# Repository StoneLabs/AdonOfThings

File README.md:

# AdonOfThings

Simple Project to turn an old industrial adon light into a multi purpose indicator light.

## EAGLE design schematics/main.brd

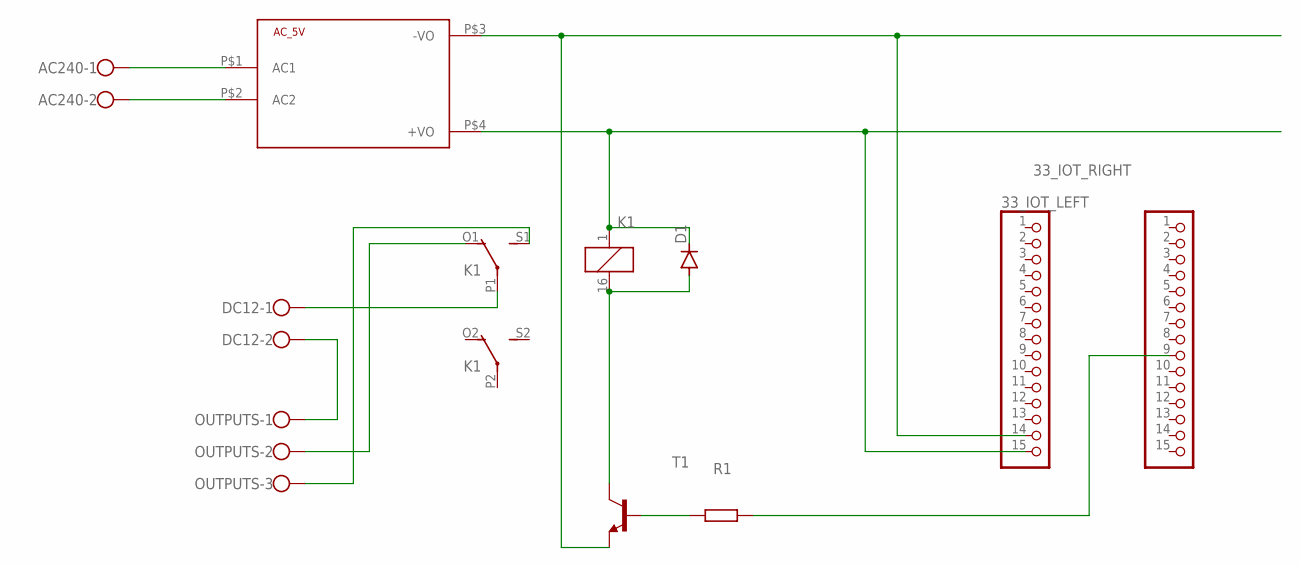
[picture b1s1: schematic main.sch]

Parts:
33_IOT_LEFT, 33_IOT_RIGHT: PINHD-1X15; 1X15
AC240: W237-102
AC_5V: HLK-PM013W; HLK-PM01
D1: 1N5060GP; DO15-12
DC12: W237-102
K1: 351
OUTPUTS: W237-103
R1: R-EU_0207/10; 0207/10
T1: 2N2222; TO18

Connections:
unnamed: AC240.1, AC_5V.P$1 (AC1)
unnamed: AC240.2, AC_5V.P$2 (AC2)
unnamed: R1.1, T1.2 (B)
unnamed: 33_IOT_LEFT.15, AC_5V.P$4 (+VO), D1.C, K1.1
unnamed: D1.A, K1.16 (2), T1.3 (C)
unnamed: DC12.2, OUTPUTS.1
unnamed: 33_IOT_LEFT.14, AC_5V.P$3 (-VO), T1.1 (E)
unnamed: DC12.1, K1.P1
unnamed: K1.O1 (O), OUTPUTS.2
unnamed: K1.S1 (S), OUTPUTS.3
unnamed: 33_IOT_RIGHT.9, R1.2

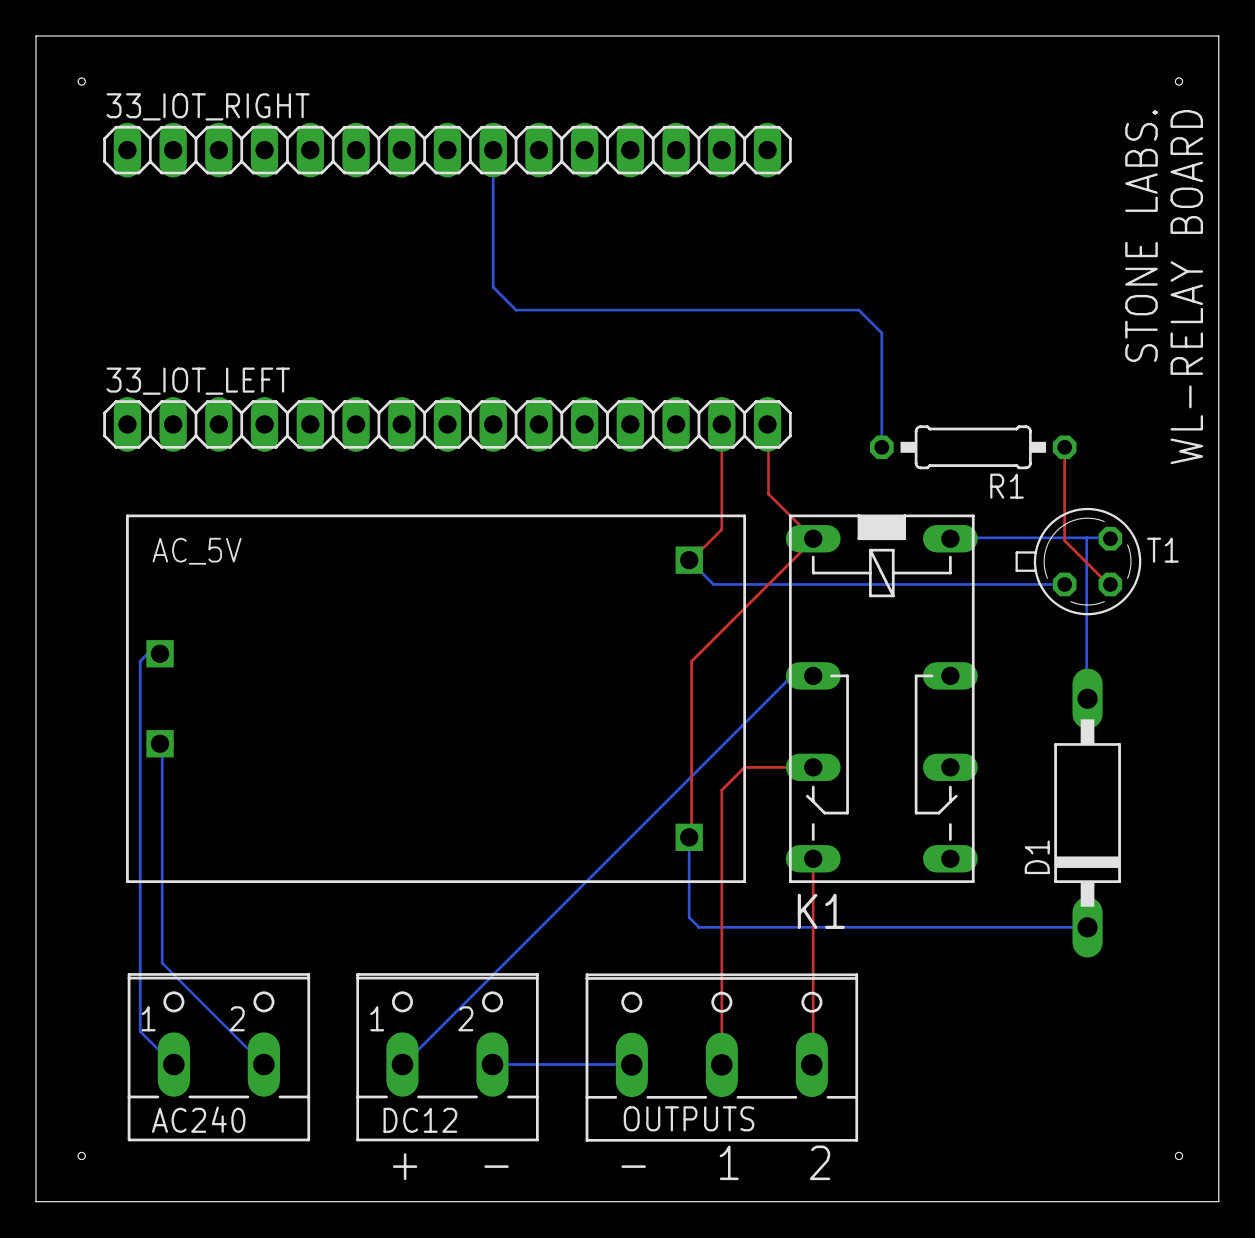
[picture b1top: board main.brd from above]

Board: 2 copper layers, 65.7 x 64.8 mm, 10 parts (0 on the bottom side), 11 nets.

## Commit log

2020-04-13 Added Project files
2020-05-06 Added Readme
